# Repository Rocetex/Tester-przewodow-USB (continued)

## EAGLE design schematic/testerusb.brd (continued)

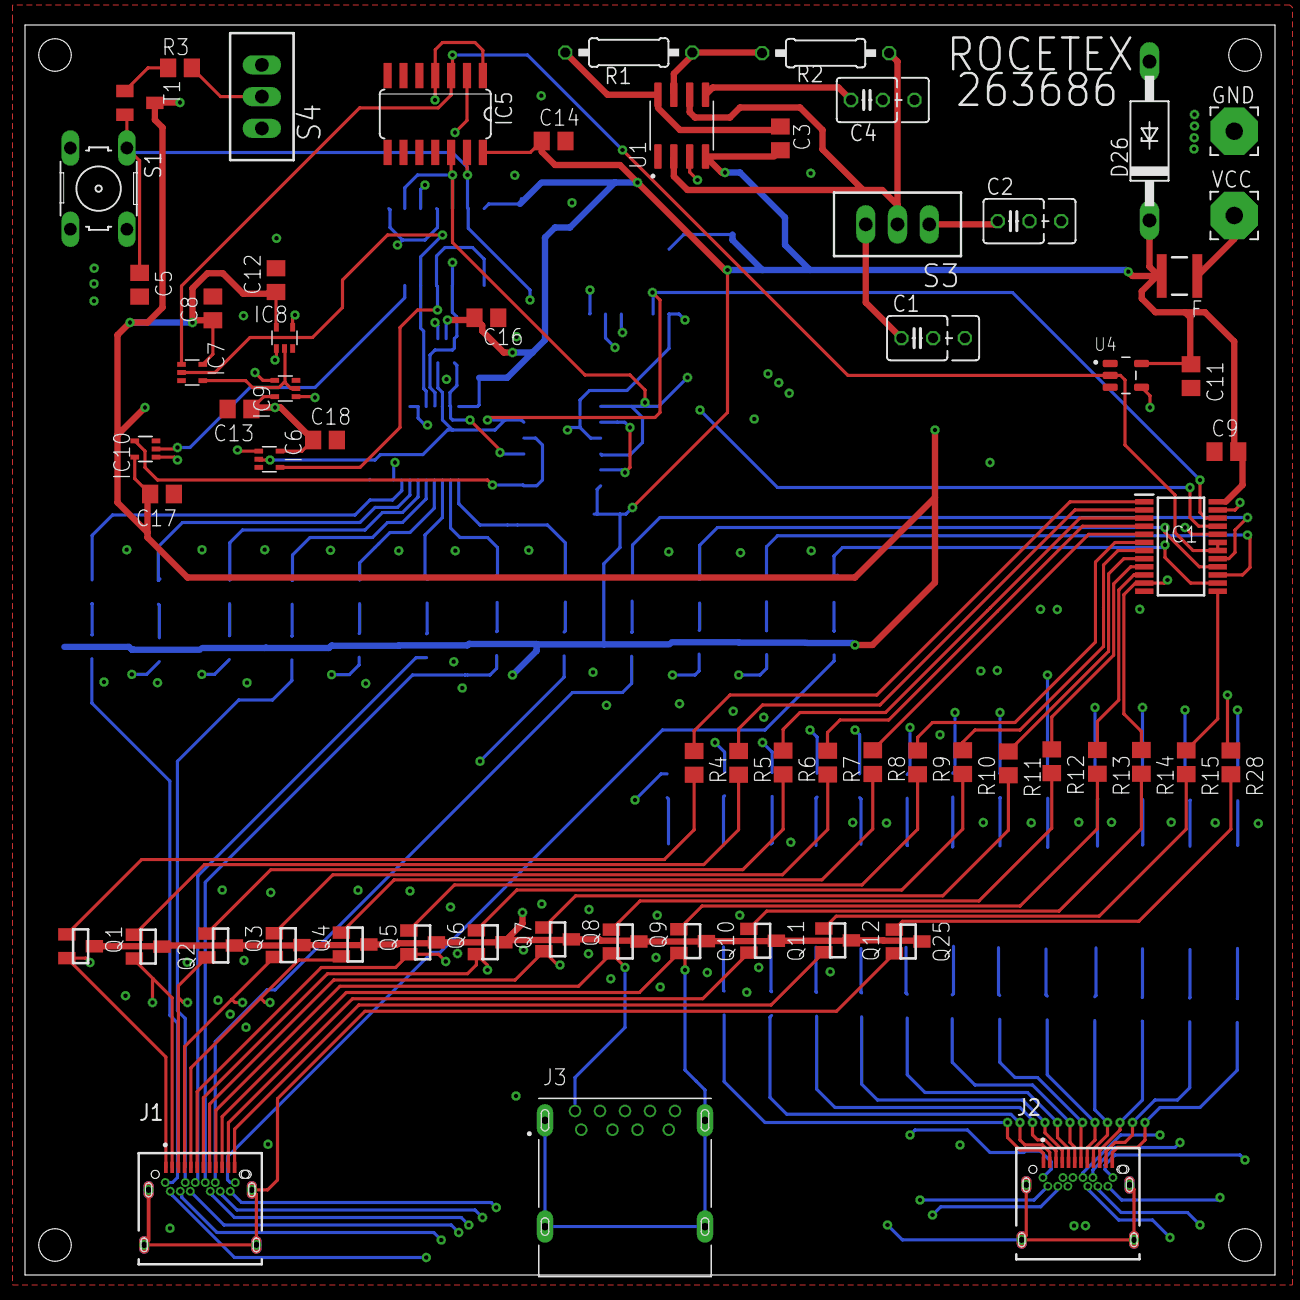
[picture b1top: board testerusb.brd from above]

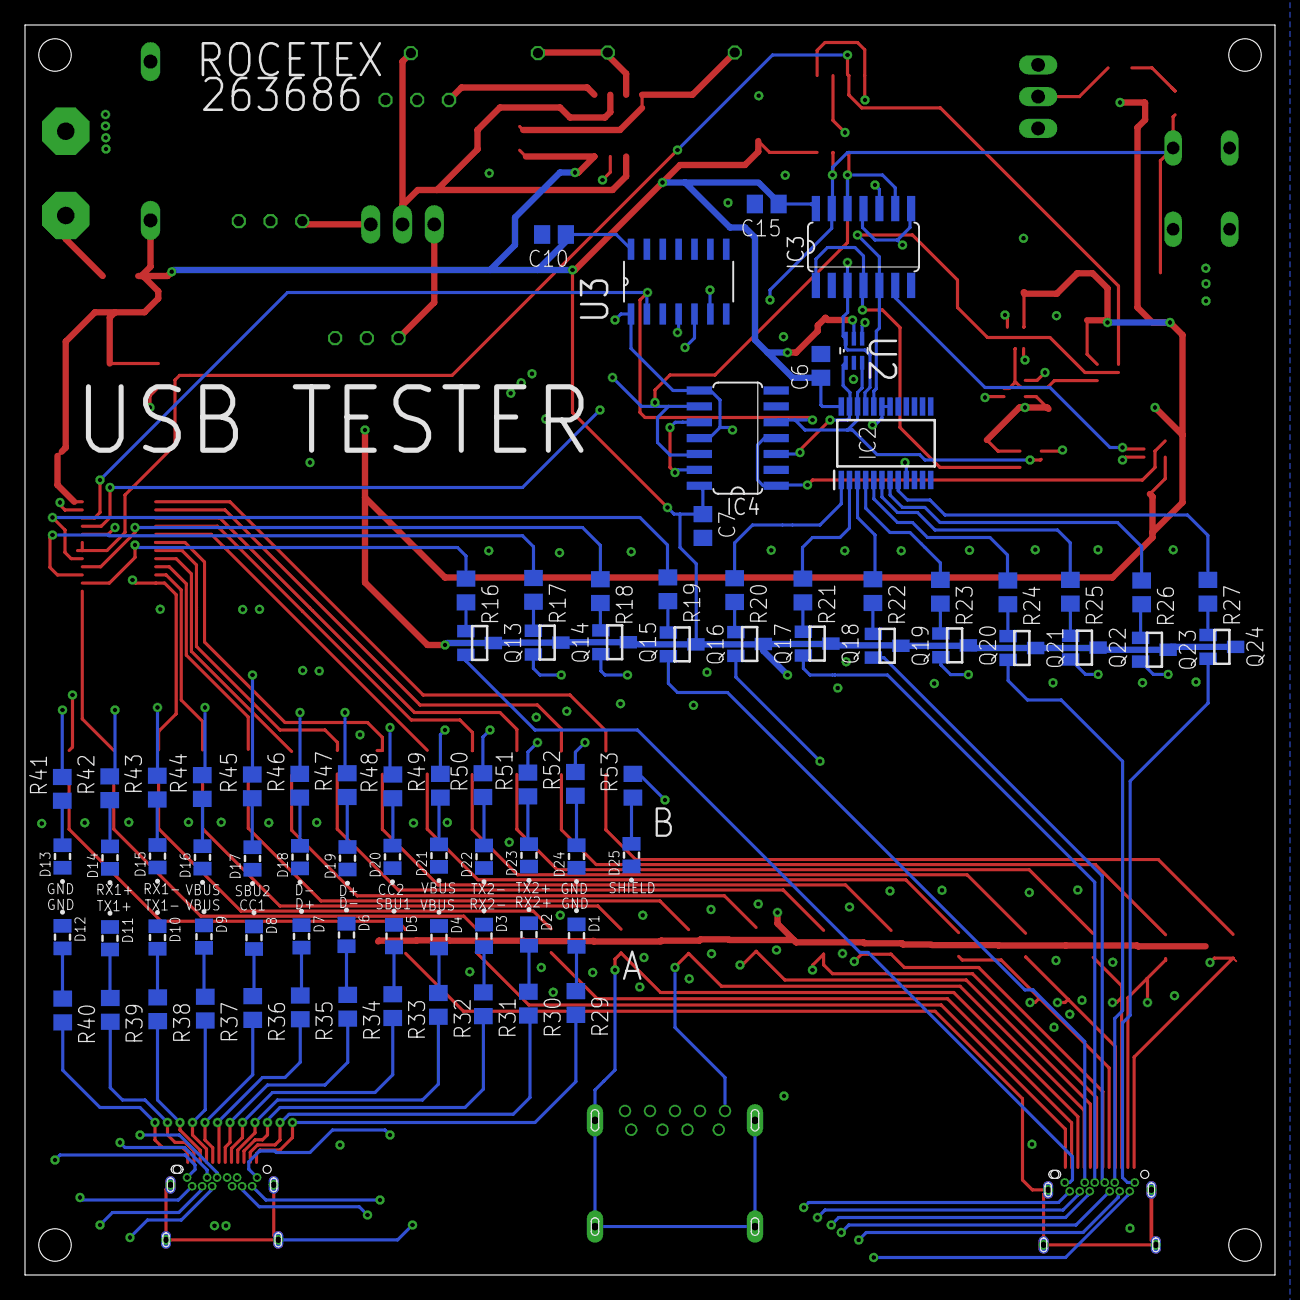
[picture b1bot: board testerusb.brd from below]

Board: 4 copper layers, 100.0 x 100.0 mm, 146 parts (83 on the bottom side), 145 nets.
